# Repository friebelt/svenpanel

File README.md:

# svenpanel
Hardware Version of the Shrine (originally made by  cubuss)<br>
https://theshrine.pw/<br>
https://svenpanel.de/<br>
https://github.com/kidzki/theshrine_v3<br>

Pictures and documentation will follow (hopefully)

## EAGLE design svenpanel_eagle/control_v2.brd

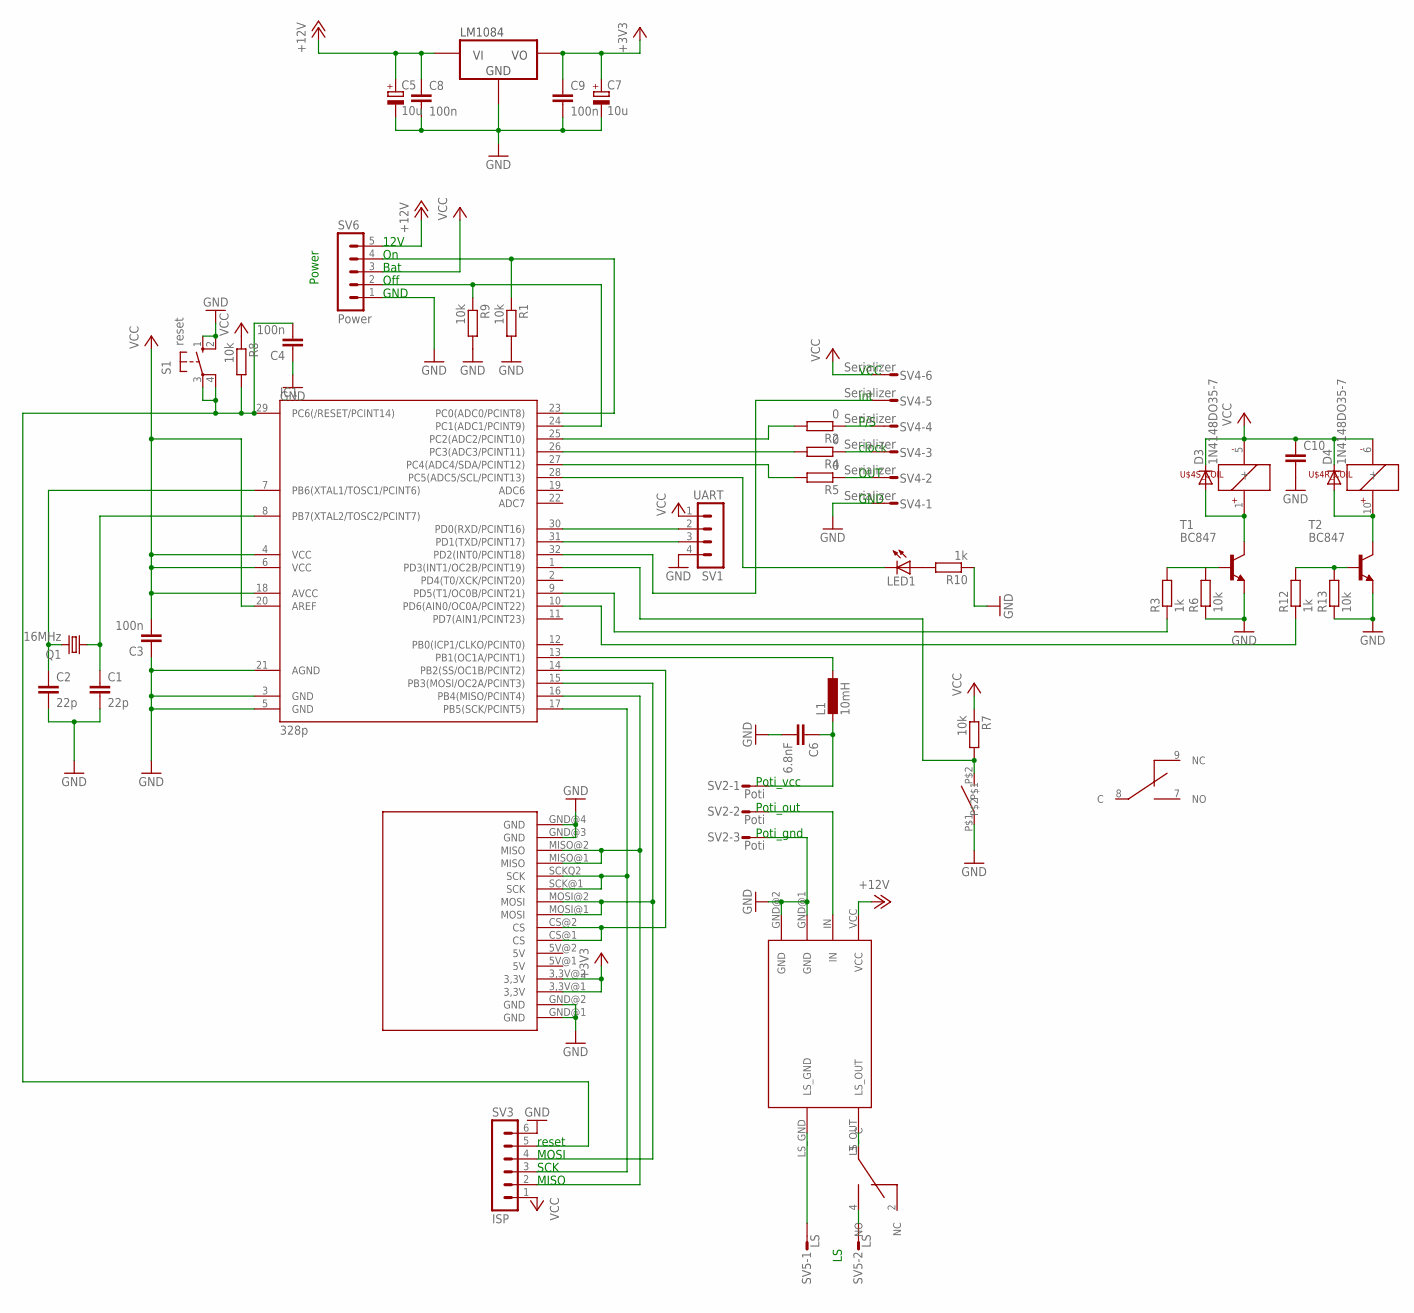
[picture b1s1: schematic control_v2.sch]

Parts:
C1, C2: 22p; C1206
C3, C4, C8, C9: 100n; C1206
C5, C7: 10u; E2,5-7
C6: 6.8nF; C050-024X044
C10: C-EUC1206; C1206
D3, D4: 1N4148DO35-7; DO35-7
IC1: 328p; TQFP32-08
L1: 10mH; 0207/5V
LED1: LEDCHIPLED_1206; CHIPLED_1206
Q1: 16MHz; HC49UP
R1, R6, R7, R8, R9, R13: 10k; M1206
R2, R4, R5: 0; M1206
R3, R10, R12: 1k; M1206
S1: reset; B3F-10XX
SV1: UART; MA04-1
SV2: Poti; S03P
SV3: ISP; MA06-1
SV4: Serializer; S06P
SV5: LS; S02P
SV6: Power; MA05-1
T1, T2: BC847; SOT23-BEC
U$1: TILT
U$2: AMP
U$3: SD_CARD_HOLDER
U$4: EB2-4.5TNU; 10PIN_SMD_RELAY
U$5: LD1117; TO220V

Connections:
+3V3: C7.+, C9.1, U$3.3,3V@1 (3,3V), U$3.3,3V@2 (3,3V), U$5.2 (VO)
+12V: C5.+, C8.1, SV6.5, U$2.VCC, U$5.3 (VI)
GND: C1.2, C2.2, C3.1, C4.1, C5.-, C6.2, C7.-, C8.2, C9.2, C10.2, IC1.3 (GND), IC1.5 (GND), IC1.21 (AGND), R1.2, R6.1, R9.2, R10.1, R13.1, S1.1 (S), S1.2 (S1), SV1.4, SV2.3, SV3.6, SV4.1, SV6.1, T1.E, T2.E, U$1.P$1, U$2.GND@1 (GND), U$2.GND@2 (GND), U$3.GND@1 (GND), U$3.GND@2 (GND), U$3.GND@3 (GND), U$3.GND@4 (GND), U$5.1 (GND)
unnamed: U$2.LS_OUT, U$4.3 (C)
unnamed: IC1.30 (PD0(RXD/PCINT16)), SV1.2
unnamed: IC1.31 (PD1(TXD/PCINT17)), SV1.3
unnamed: C2.1, IC1.7 (PB6(XTAL1/TOSC1/PCINT6)), Q1.2
unnamed: C1.1, IC1.8 (PB7(XTAL2/TOSC2/PCINT7)), Q1.1
unnamed: IC1.14 (PB2(SS/OC1B/PCINT2)), U$3.CS@1 (CS), U$3.CS@2 (CS)
unnamed: IC1.15 (PB3(MOSI/OC2A/PCINT3)), SV3.4, U$3.MOSI@1 (MOSI), U$3.MOSI@2 (MOSI)
unnamed: IC1.16 (PB4(MISO/PCINT4)), SV3.2, U$3.MISO@1 (MISO), U$3.MISO@2 (MISO)
unnamed: IC1.17 (PB5(SCK/PCINT5)), SV3.3, U$3.SCK@1 (SCK), U$3.SCKQ2 (SCK)
unnamed: SV5.2, U$4.4 (NO)
unnamed: IC1.13 (PB1(OC1A/PCINT1)), L1.1
unnamed: C6.1, L1.2, SV2.1
unnamed: SV5.1, U$2.LS_GND
unnamed: SV2.2, U$2.IN
unnamed: IC1.23 (PC0(ADC0/PCINT8)), R1.1, SV6.4
unnamed: R5.1, SV4.2
unnamed: R4.1, SV4.3
unnamed: R2.1, SV4.4
unnamed: IC1.32 (PD2(INT0/PCINT18)), SV4.5
unnamed: IC1.25 (PC2(ADC2/PCINT10)), R2.2
unnamed: IC1.26 (PC3(ADC3/PCINT11)), R4.2
unnamed: IC1.24 (PC1(ADC1/PCINT9)), R9.1, SV6.2
unnamed: D3.A, T1.C, U$4.1 (+)
unnamed: IC1.27 (PC4(ADC4/SDA/PCINT12)), R5.2
unnamed: IC1.1 (PD3(INT1/OC2B/PCINT19)), R7.2, U$1.P$2
unnamed: LED1.A, R10.2
unnamed: R12.2, R13.2, T2.B
unnamed: IC1.28 (PC5(ADC5/SCL/PCINT13)), LED1.C
unnamed: IC1.10 (PD6(AIN0/OC0A/PCINT22)), R12.1
unnamed: C4.2, IC1.29 (PC6(/RESET/PCINT14)), R8.2, S1.3, S1.4 (P1), SV3.5
unnamed: IC1.9 (PD5(T1/OC0B/PCINT21)), R3.1
unnamed: D4.A, T2.C, U$4.10 (+)
unnamed: R3.2, R6.2, T1.B
VCC: C3.2, C10.1, D3.C, D4.C, IC1.4 (VCC), IC1.6 (VCC), IC1.18 (AVCC), IC1.20 (AREF), R7.1, R8.1, SV1.1, SV3.1, SV4.6, SV6.3, U$4.5 (-), U$4.6 (-)

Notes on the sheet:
Poti_vcc
Poti_out
Poti_gnd
12V
Off
GND
Bat
OUT
clock
P/S
int
VCC
Power
reset
MOSI
SCK
MISO

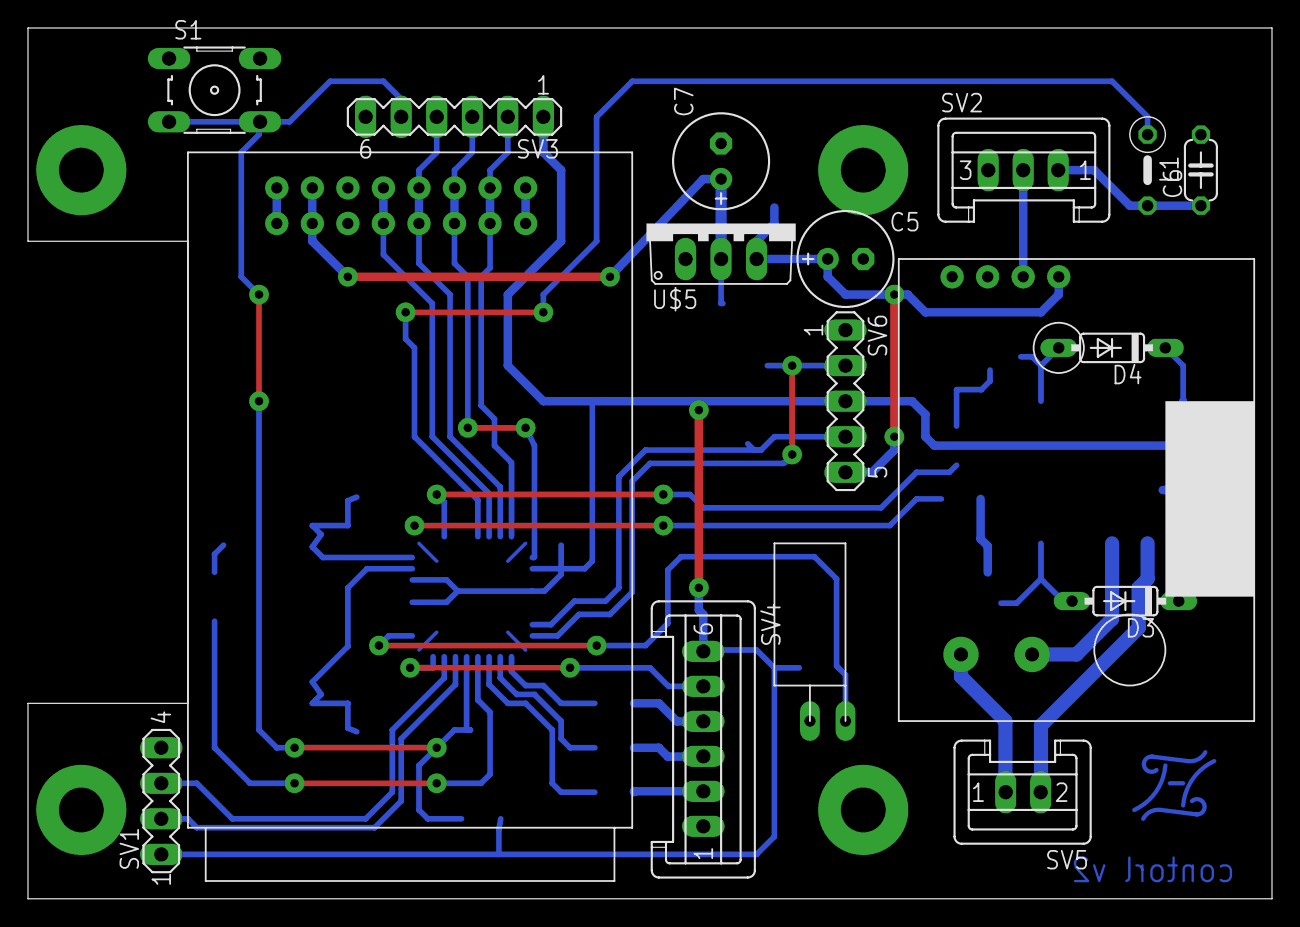
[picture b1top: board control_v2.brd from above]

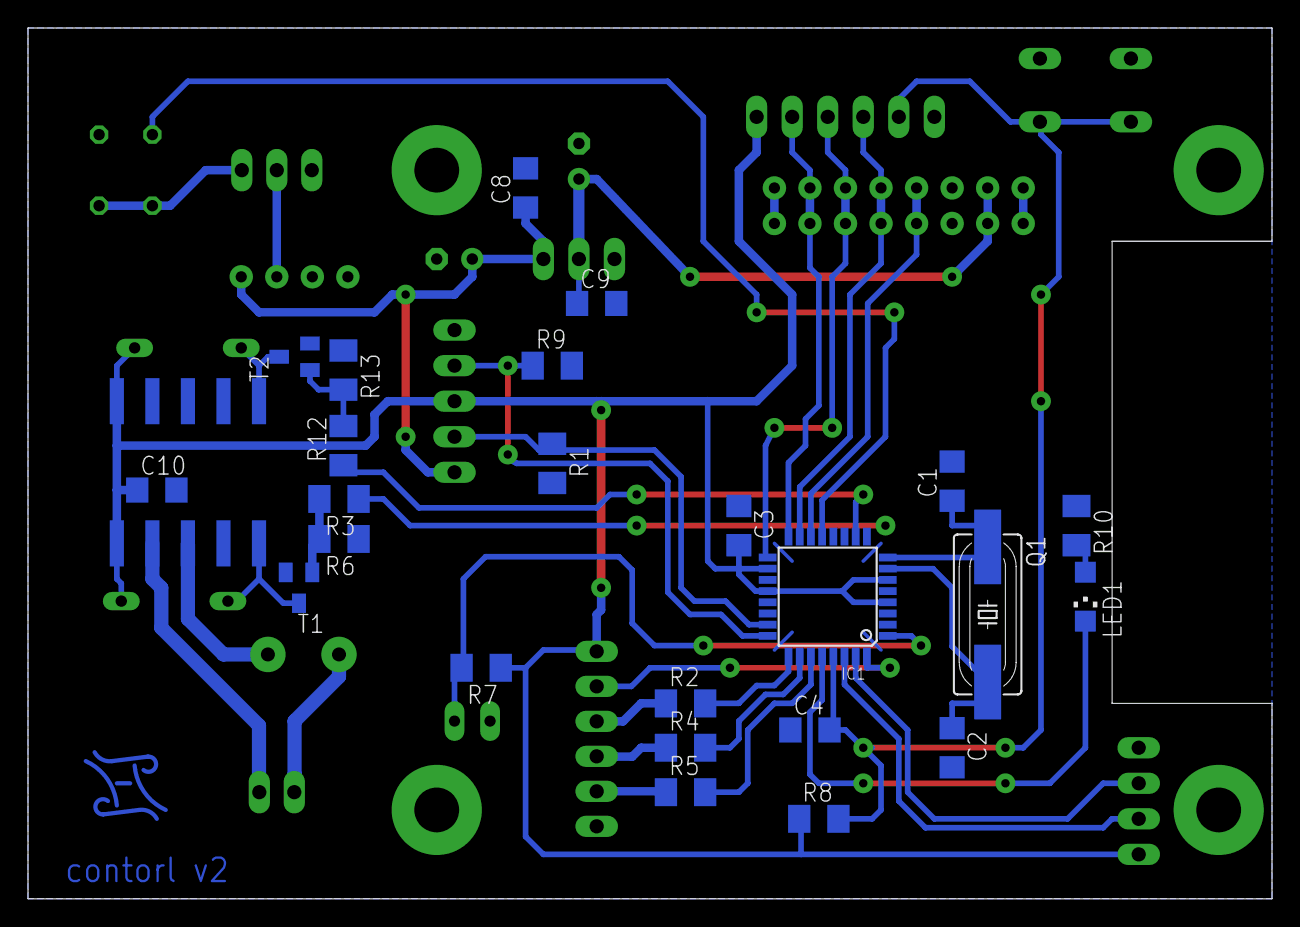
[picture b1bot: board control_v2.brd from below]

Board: 2 copper layers, 88.9 x 62.2 mm, 42 parts (25 on the bottom side), 37 nets.

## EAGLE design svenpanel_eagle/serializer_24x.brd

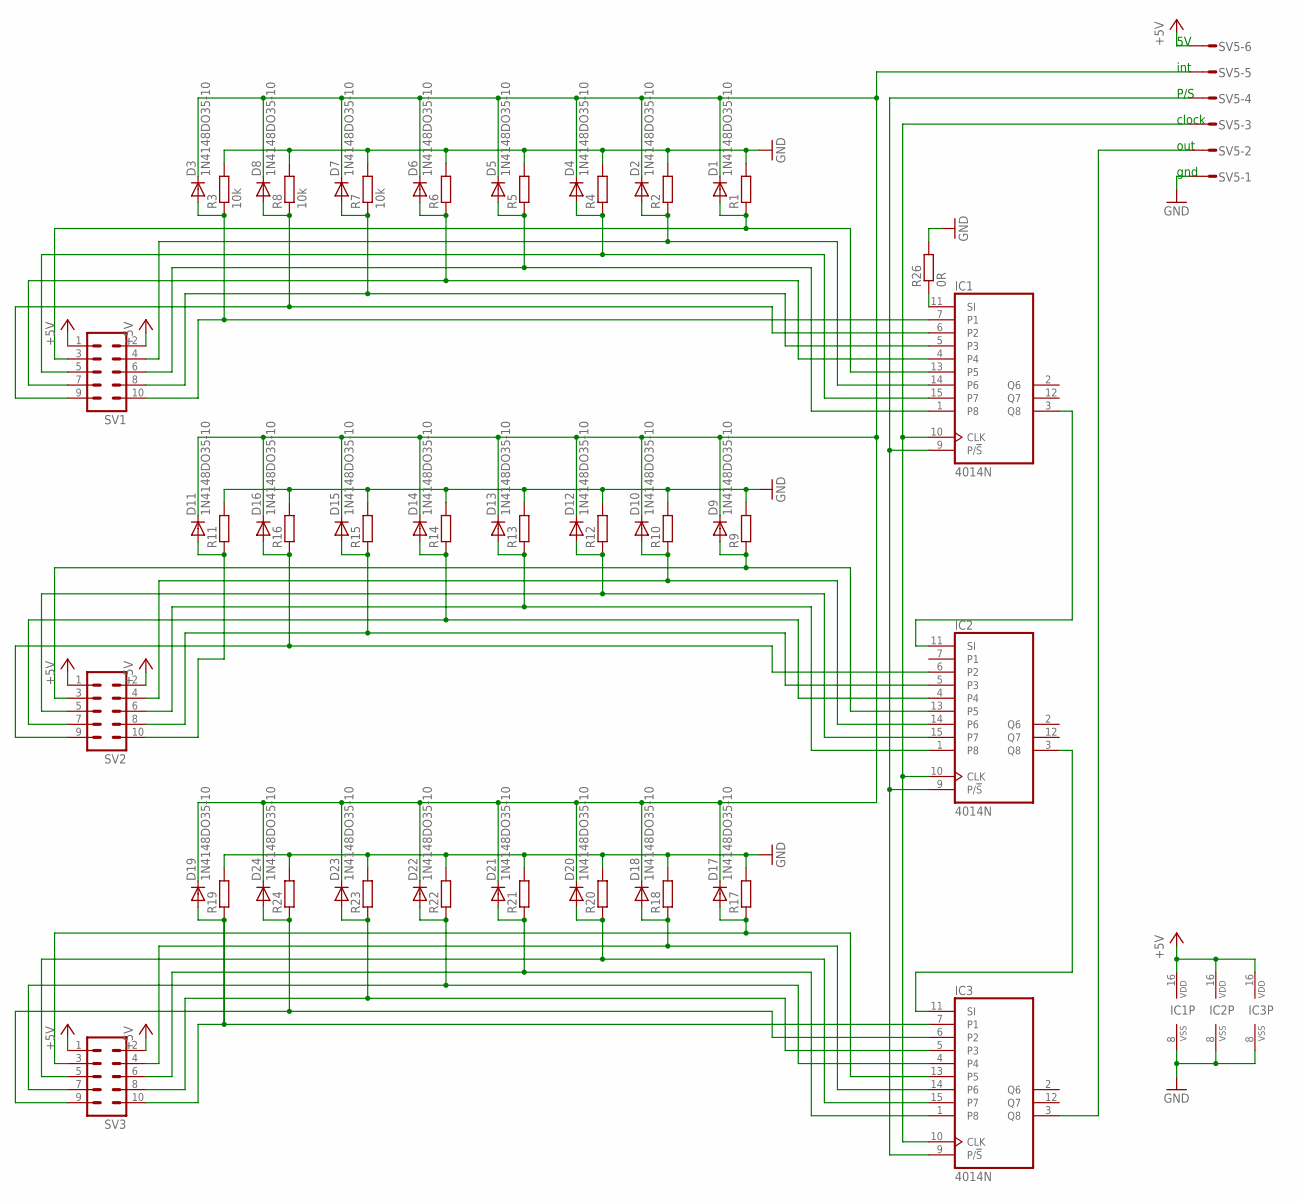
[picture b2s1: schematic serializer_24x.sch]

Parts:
D1, D2, D3, D4, D5, D6, D7, D8, D9, D10, D11, D12, D13, D14, D15, D16, D17, D18, D19, D20, D21, D22, D23, D24: 1N4148DO35-10; DO35-10
IC1, IC2, IC3: 4014N; DIL16
R1, R2, R4, R5, R6, R9, R10, R11, R12, R13, R14, R15, R16, R17, R18, R19, R20, R21, R22, R23, R24: R-EU_M1206; M1206
R3, R7, R8: 10k; M1206
R26: 0R; M1206
SV1, SV2, SV3: ML10
SV5: S06P

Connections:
+5V: IC1.16 (VDD), IC2.16 (VDD), IC3.16 (VDD), SV1.1, SV1.2, SV2.1, SV2.2, SV3.1, SV3.2, SV5.6
GND: IC1.8 (VSS), IC2.8 (VSS), IC3.8 (VSS), R1.2, R2.2, R3.2, R4.2, R5.2, R6.2, R7.2, R8.2, R9.2, R10.2, R11.2, R12.2, R13.2, R14.2, R15.2, R16.2, R17.2, R18.2, R19.2, R20.2, R21.2, R22.2, R23.2, R24.2, R26.2, SV5.1
unnamed: D1.A, IC1.13 (P5), R1.1, SV1.3
unnamed: D2.A, IC1.14 (P6), R2.1, SV1.4
unnamed: D9.A, IC2.13 (P5), R9.1, SV2.3
unnamed: D10.A, IC2.14 (P6), R10.1, SV2.4
unnamed: D12.A, IC2.15 (P7), R12.1, SV2.5
unnamed: D13.A, IC2.1 (P8), R13.1, SV2.6
unnamed: D14.A, IC2.4, R14.1, SV2.7
unnamed: D15.A, IC2.5 (P3), R15.1, SV2.8
unnamed: D16.A, IC2.6 (P2), R16.1, SV2.9
unnamed: IC2.3 (Q8), IC3.11 (SI)
unnamed: IC1.10 (CLK), IC2.10 (CLK), IC3.10 (CLK), SV5.3
unnamed: D17.A, IC3.13 (P5), R17.1, SV3.3
unnamed: D18.A, IC3.14 (P6), R18.1, SV3.4
unnamed: D1.C, D2.C, D3.C, D4.C, D5.C, D6.C, D7.C, D8.C, D9.C, D10.C, D11.C, D12.C, D13.C, D14.C, D15.C, D16.C, D17.C, D18.C, D19.C, D20.C, D21.C, D22.C, D23.C, D24.C, SV5.5
unnamed: D19.A, IC3.7 (P1), R19.1, SV3.10
unnamed: D20.A, IC3.15 (P7), R20.1, SV3.5
unnamed: D21.A, IC3.1 (P8), R21.1, SV3.6
unnamed: D22.A, IC3.4, R22.1, SV3.7
unnamed: D23.A, IC3.5 (P3), R23.1, SV3.8
unnamed: D24.A, IC3.6 (P2), R24.1, SV3.9
unnamed: IC1.11 (SI), R26.1
unnamed: D11.A, R11.1, SV2.10
unnamed: IC3.3 (Q8), SV5.2
unnamed: D3.A, IC1.7 (P1), R3.1, SV1.10
unnamed: IC1.9 (P/!S), IC2.9 (P/!S), IC3.9 (P/!S), SV5.4
unnamed: D4.A, IC1.15 (P7), R4.1, SV1.5
unnamed: D5.A, IC1.1 (P8), R5.1, SV1.6
unnamed: D6.A, IC1.4, R6.1, SV1.7
unnamed: D7.A, IC1.5 (P3), R7.1, SV1.8
unnamed: D8.A, IC1.6 (P2), R8.1, SV1.9
unnamed: IC1.3 (Q8), IC2.11 (SI)

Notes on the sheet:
out
clock
gnd
P/S
int

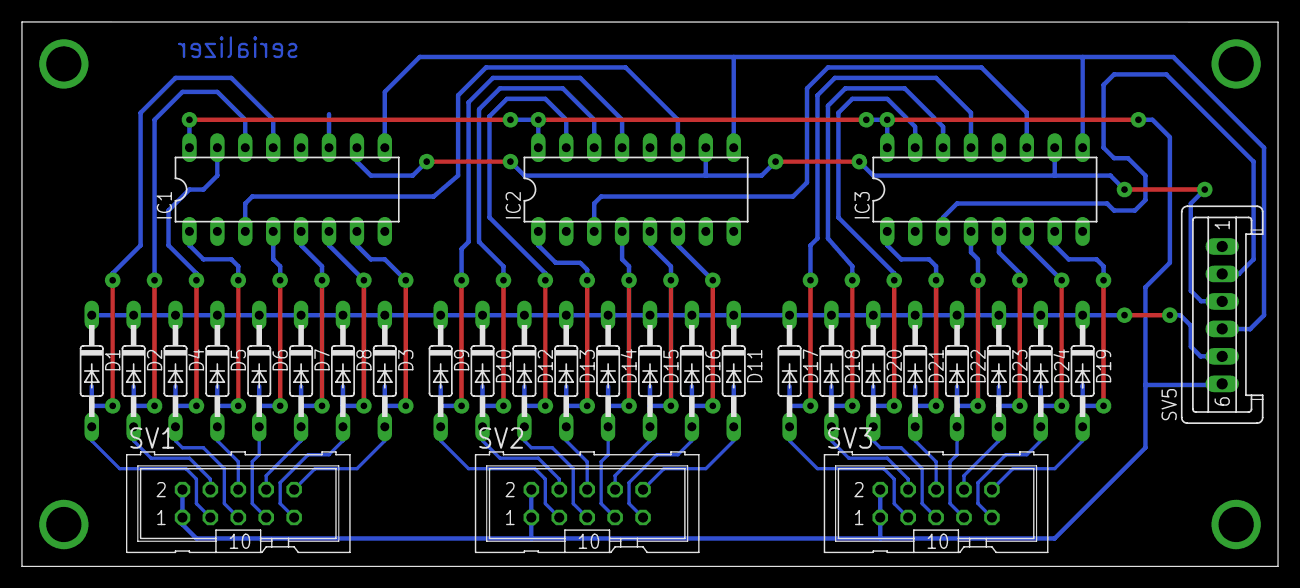
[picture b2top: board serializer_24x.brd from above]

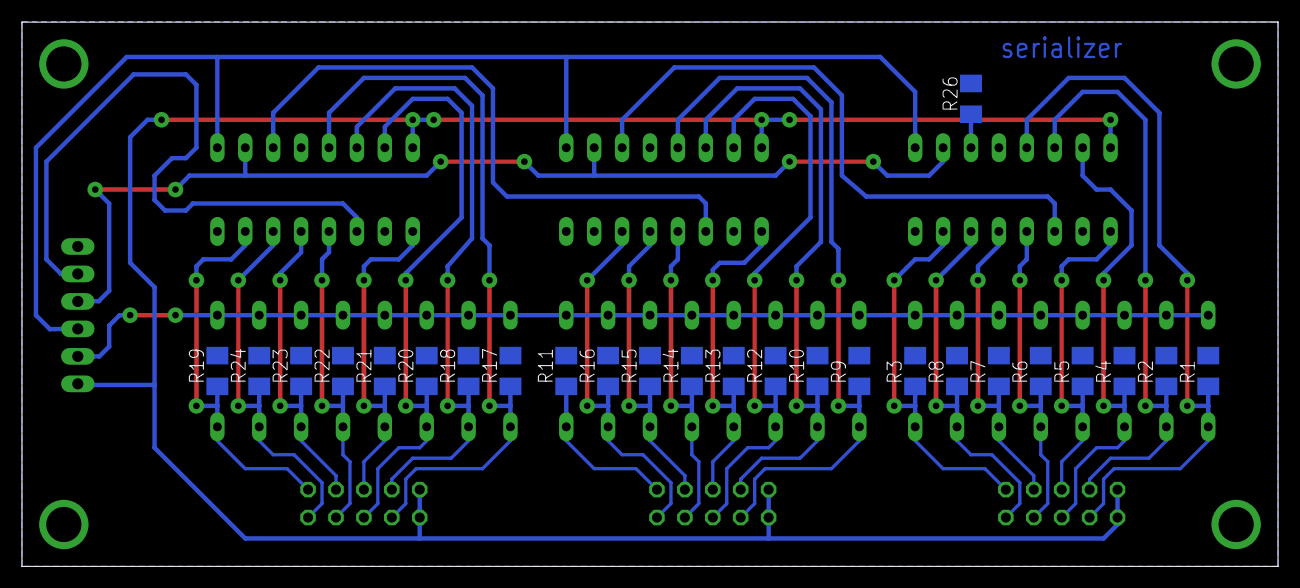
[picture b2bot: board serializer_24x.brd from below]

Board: 2 copper layers, 114.3 x 49.5 mm, 56 parts (25 on the bottom side), 33 nets.

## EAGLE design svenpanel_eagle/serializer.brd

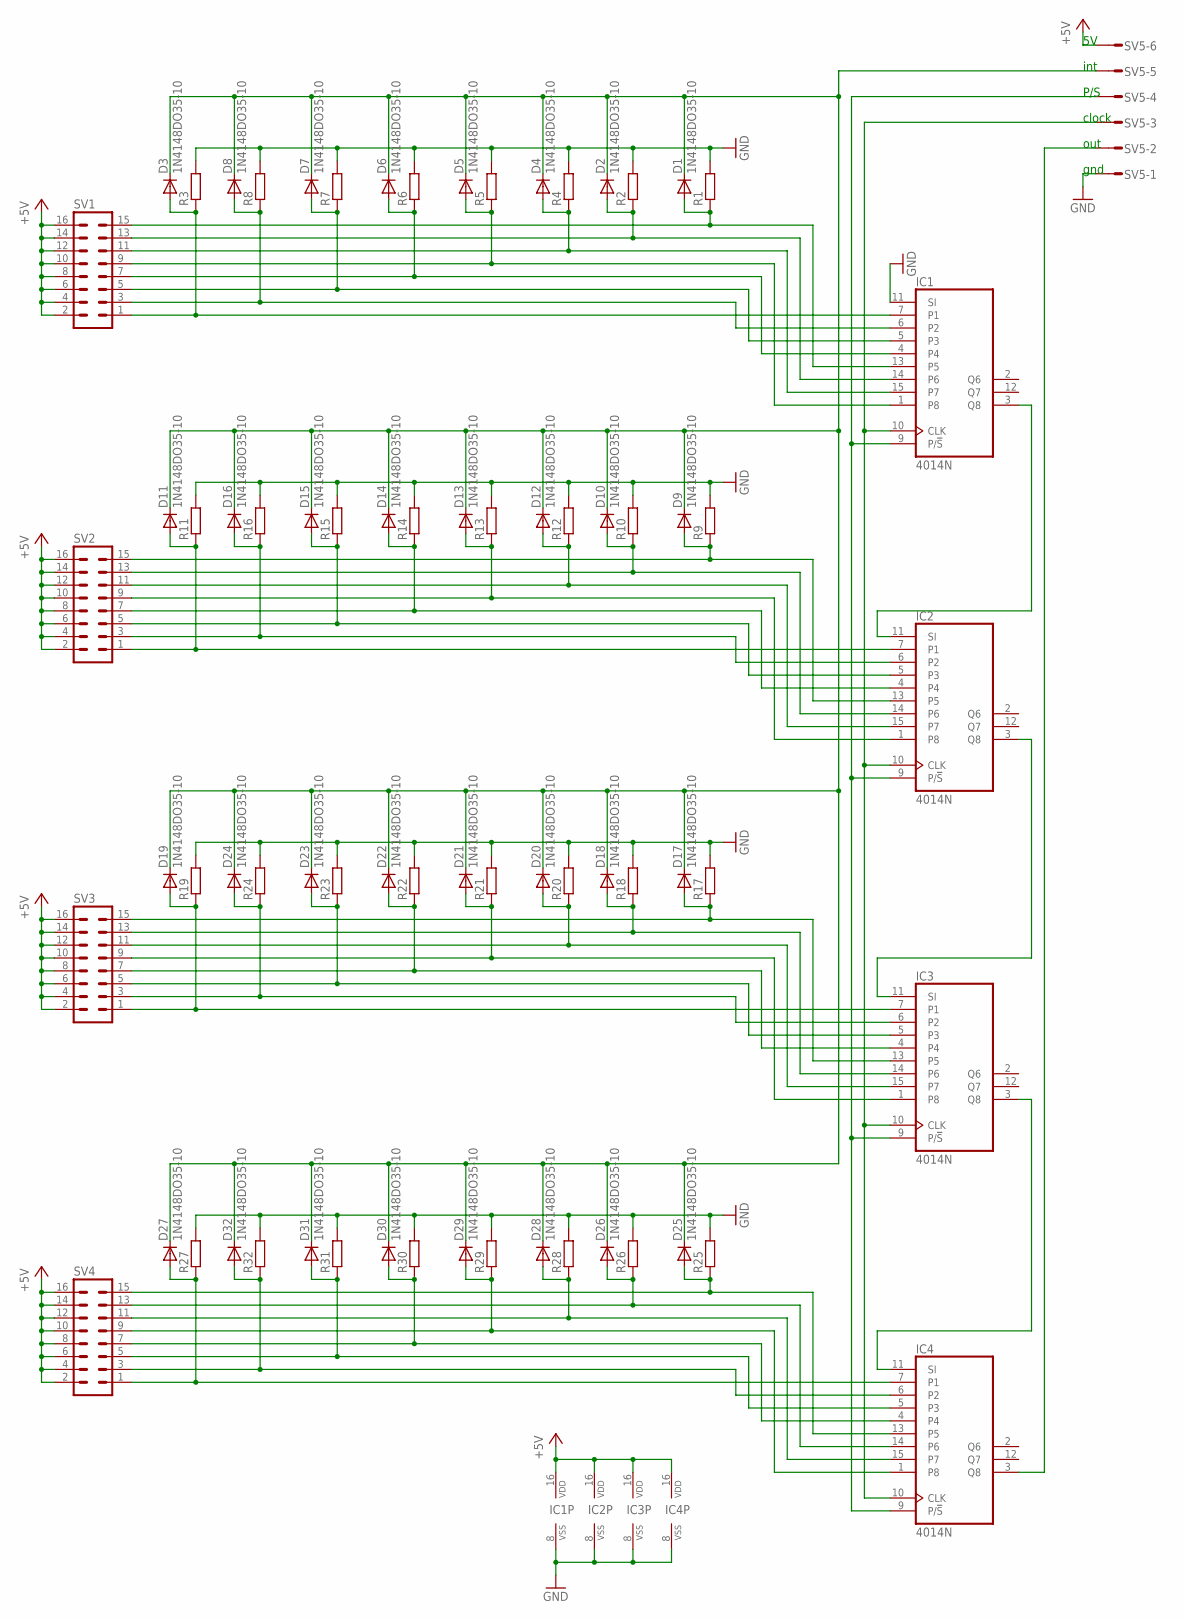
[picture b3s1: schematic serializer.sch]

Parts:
D1, D2, D3, D4, D5, D6, D7, D8, D9, D10, D11, D12, D13, D14, D15, D16, D17, D18, D19, D20, D21, D22, D23, D24, D25, D26, D27, D28, D29, D30, D31, D32: 1N4148DO35-10; DO35-10
IC1, IC2, IC3, IC4: 4014N; DIL16
R1, R2, R3, R4, R5, R6, R7, R8, R9, R10, R11, R12, R13, R14, R15, R16, R17, R18, R19, R20, R21, R22, R23, R24, R25, R26, R27, R28, R29, R30, R31, R32: R-EU_M1206; M1206
SV1, SV2, SV3, SV4: MA08-2
SV5: S06P

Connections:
+5V: IC1.16 (VDD), IC2.16 (VDD), IC3.16 (VDD), IC4.16 (VDD), SV1.2, SV1.4, SV1.6, SV1.8, SV1.10, SV1.12, SV1.14, SV1.16, SV2.2, SV2.4, SV2.6, SV2.8, SV2.10, SV2.12, SV2.14, SV2.16, SV3.2, SV3.4, SV3.6, SV3.8, SV3.10, SV3.12, SV3.14, SV3.16, SV4.2, SV4.4, SV4.6, SV4.8, SV4.10, SV4.12, SV4.14, SV4.16, SV5.6
GND: IC1.8 (VSS), IC1.11 (SI), IC2.8 (VSS), IC3.8 (VSS), IC4.8 (VSS), R1.2, R2.2, R3.2, R4.2, R5.2, R6.2, R7.2, R8.2, R9.2, R10.2, R11.2, R12.2, R13.2, R14.2, R15.2, R16.2, R17.2, R18.2, R19.2, R20.2, R21.2, R22.2, R23.2, R24.2, R25.2, R26.2, R27.2, R28.2, R29.2, R30.2, R31.2, R32.2, SV5.1
unnamed: D1.A, IC1.13 (P5), R1.1, SV1.15
unnamed: D2.A, IC1.14 (P6), R2.1, SV1.13
unnamed: D9.A, IC2.13 (P5), R9.1, SV2.15
unnamed: D10.A, IC2.14 (P6), R10.1, SV2.13
unnamed: D11.A, IC2.7 (P1), R11.1, SV2.1
unnamed: D12.A, IC2.15 (P7), R12.1, SV2.11
unnamed: D13.A, IC2.1 (P8), R13.1, SV2.9
unnamed: D14.A, IC2.4, R14.1, SV2.7
unnamed: D15.A, IC2.5 (P3), R15.1, SV2.5
unnamed: D16.A, IC2.6 (P2), R16.1, SV2.3
unnamed: IC2.3 (Q8), IC3.11 (SI)
unnamed: IC1.10 (CLK), IC2.10 (CLK), IC3.10 (CLK), IC4.10 (CLK), SV5.3
unnamed: D17.A, IC3.13 (P5), R17.1, SV3.15
unnamed: D18.A, IC3.14 (P6), R18.1, SV3.13
unnamed: D1.C, D2.C, D3.C, D4.C, D5.C, D6.C, D7.C, D8.C, D9.C, D10.C, D11.C, D12.C, D13.C, D14.C, D15.C, D16.C, D17.C, D18.C, D19.C, D20.C, D21.C, D22.C, D23.C, D24.C, D25.C, D26.C, D27.C, D28.C, D29.C, D30.C, D31.C, D32.C, SV5.5
unnamed: D19.A, IC3.7 (P1), R19.1, SV3.1
unnamed: D20.A, IC3.15 (P7), R20.1, SV3.11
unnamed: D21.A, IC3.1 (P8), R21.1, SV3.9
unnamed: D22.A, IC3.4, R22.1, SV3.7
unnamed: D23.A, IC3.5 (P3), R23.1, SV3.5
unnamed: D24.A, IC3.6 (P2), R24.1, SV3.3
unnamed: IC3.3 (Q8), IC4.11 (SI)
unnamed: D25.A, IC4.13 (P5), R25.1, SV4.15
unnamed: D26.A, IC4.14 (P6), R26.1, SV4.13
unnamed: D27.A, IC4.7 (P1), R27.1, SV4.1
unnamed: D28.A, IC4.15 (P7), R28.1, SV4.11
unnamed: D29.A, IC4.1 (P8), R29.1, SV4.9
unnamed: D30.A, IC4.4, R30.1, SV4.7
unnamed: D31.A, IC4.5 (P3), R31.1, SV4.5
unnamed: D32.A, IC4.6 (P2), R32.1, SV4.3
unnamed: IC4.3 (Q8), SV5.2
unnamed: D3.A, IC1.7 (P1), R3.1, SV1.1
unnamed: IC1.9 (P/!S), IC2.9 (P/!S), IC3.9 (P/!S), IC4.9 (P/!S), SV5.4
unnamed: D4.A, IC1.15 (P7), R4.1, SV1.11
unnamed: D5.A, IC1.1 (P8), R5.1, SV1.9
unnamed: D6.A, IC1.4, R6.1, SV1.7
unnamed: D7.A, IC1.5 (P3), R7.1, SV1.5
unnamed: D8.A, IC1.6 (P2), R8.1, SV1.3
unnamed: IC1.3 (Q8), IC2.11 (SI)

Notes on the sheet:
out
clock
gnd
P/S
int

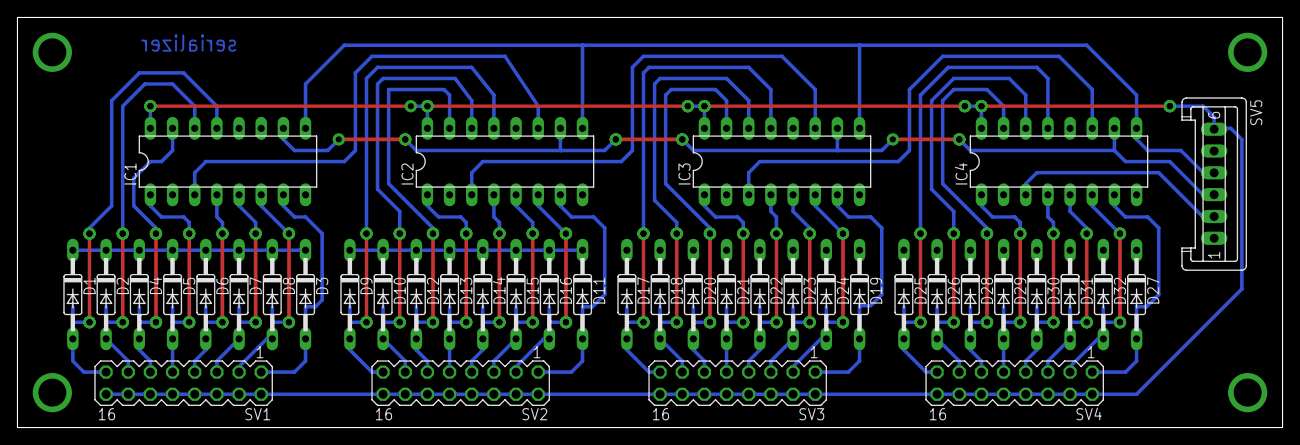
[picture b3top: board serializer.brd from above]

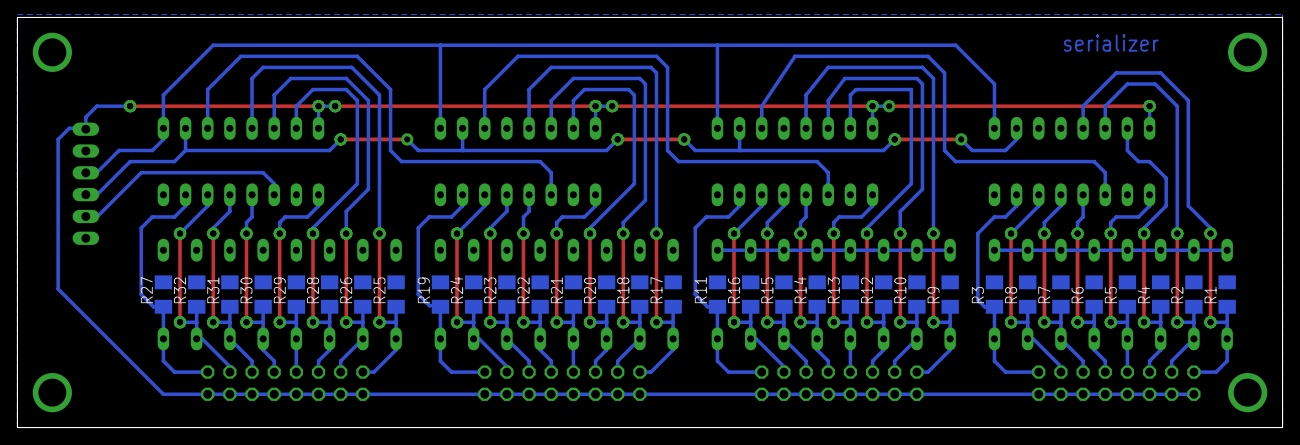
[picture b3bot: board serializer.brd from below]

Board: 2 copper layers, 145.0 x 47.0 mm, 73 parts (32 on the bottom side), 41 nets.

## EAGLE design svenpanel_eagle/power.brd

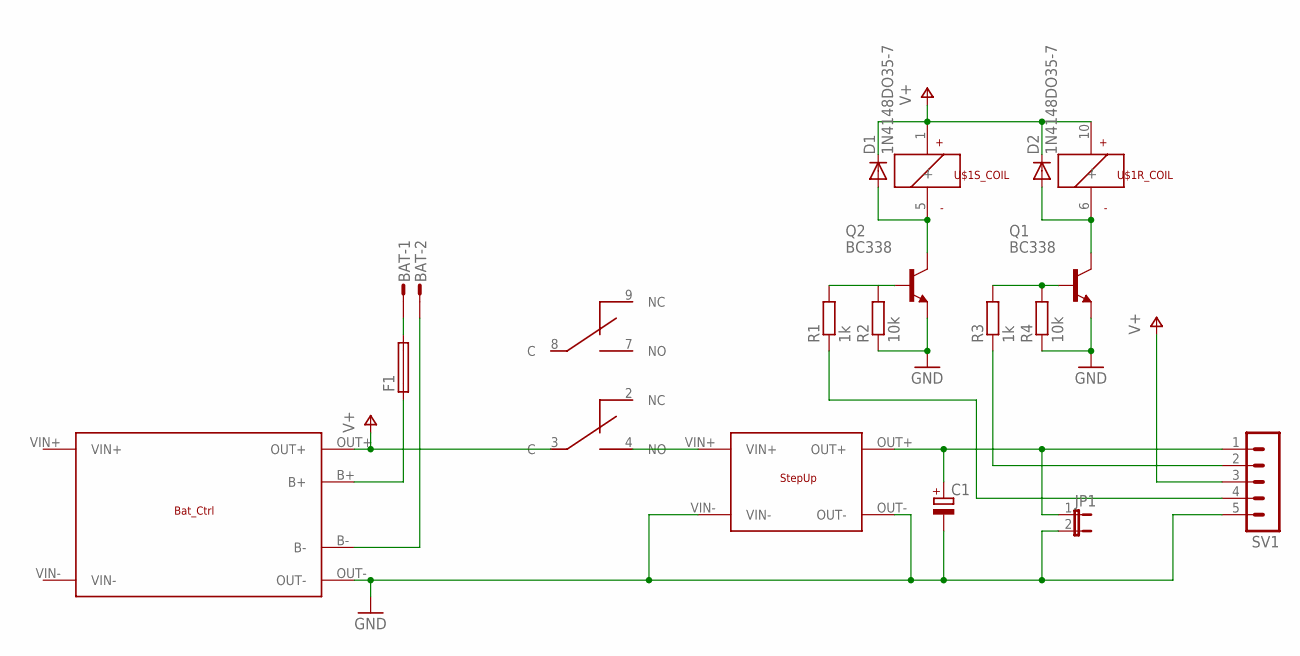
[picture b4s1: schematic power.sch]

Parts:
BAT: S02P
C1: CPOL-EUE3.5-8; E3,5-8
D1, D2: 1N4148DO35-7; DO35-7
F1: SH22,5
JP1: JP1E; JP1
Q1, Q2: BC338; TO92-EBC
R1, R3: 1k; 0204/7
R2, R4: 10k; M1206
SV1: MA05-1
U$1: EB2-4.5TNU; 10PIN_SMD_RELAY
U$2: STEP_UP
U$3: BAT_CTRL; BAT_CONTR

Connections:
GND: C1.-, JP1.2, Q1.E, Q2.E, R2.1, R4.1, SV1.5, U$2.OUT-, U$2.VIN-, U$3.OUT-
unnamed: D2.A, Q1.C, U$1.6 (-)
unnamed: D1.A, Q2.C, U$1.5 (-)
unnamed: Q2.B, R1.2, R2.2
unnamed: Q1.B, R3.2, R4.2
unnamed: BAT.1, F1.2
unnamed: F1.1, U$3.B+
unnamed: BAT.2, U$3.B-
unnamed: U$1.4 (NO), U$2.VIN+
unnamed: C1.+, JP1.1, SV1.1, U$2.OUT+
unnamed: R3.1, SV1.2
unnamed: R1.1, SV1.4
V+: D1.C, D2.C, SV1.3, U$1.1 (+), U$1.3 (C), U$1.10 (+), U$3.OUT+

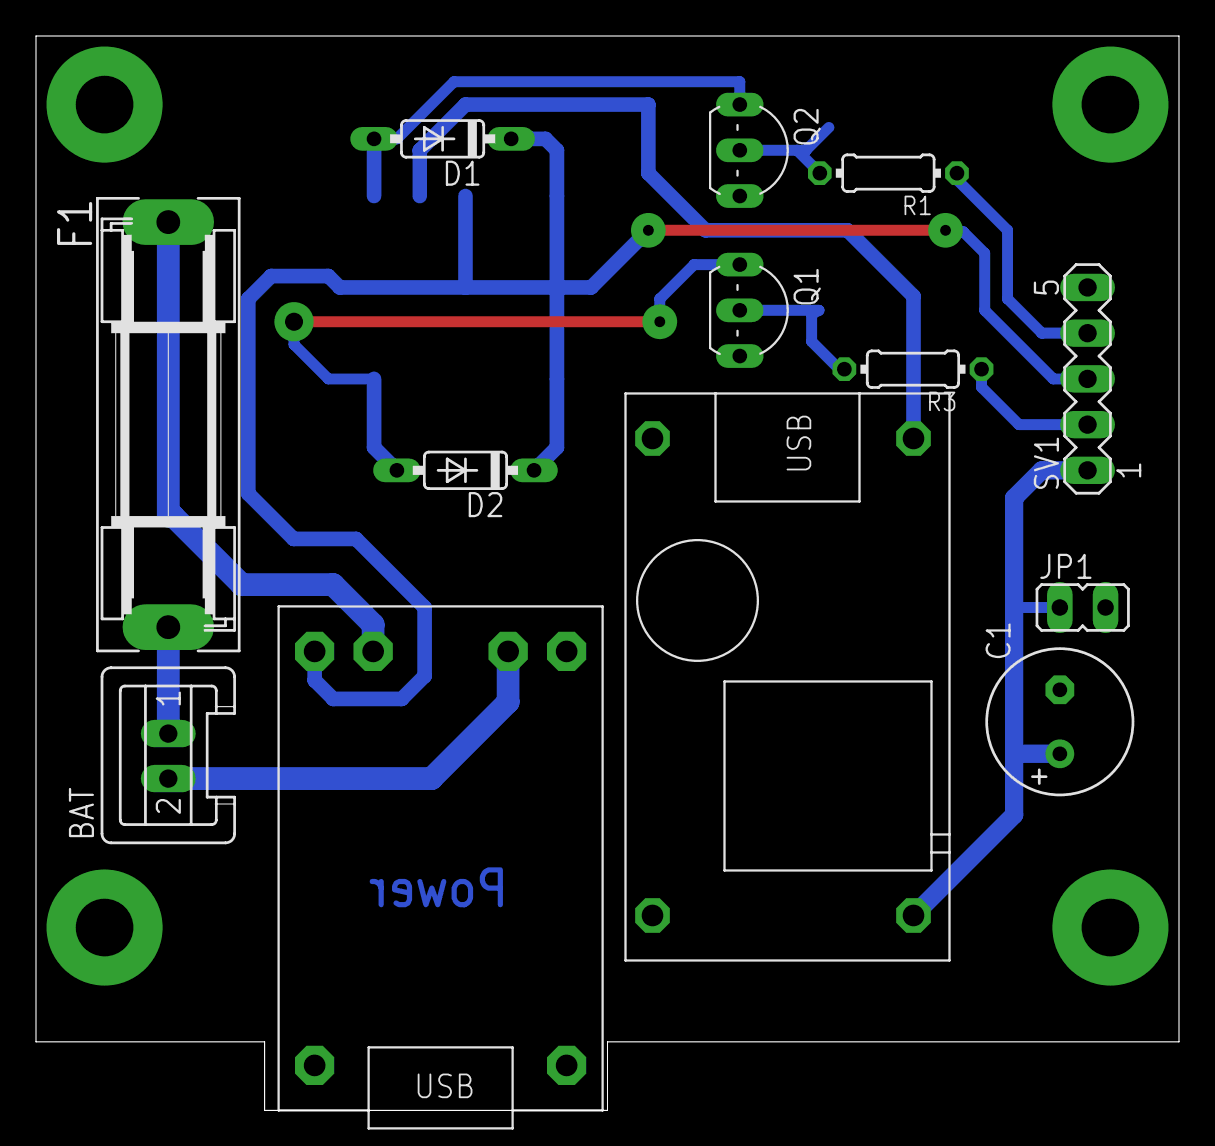
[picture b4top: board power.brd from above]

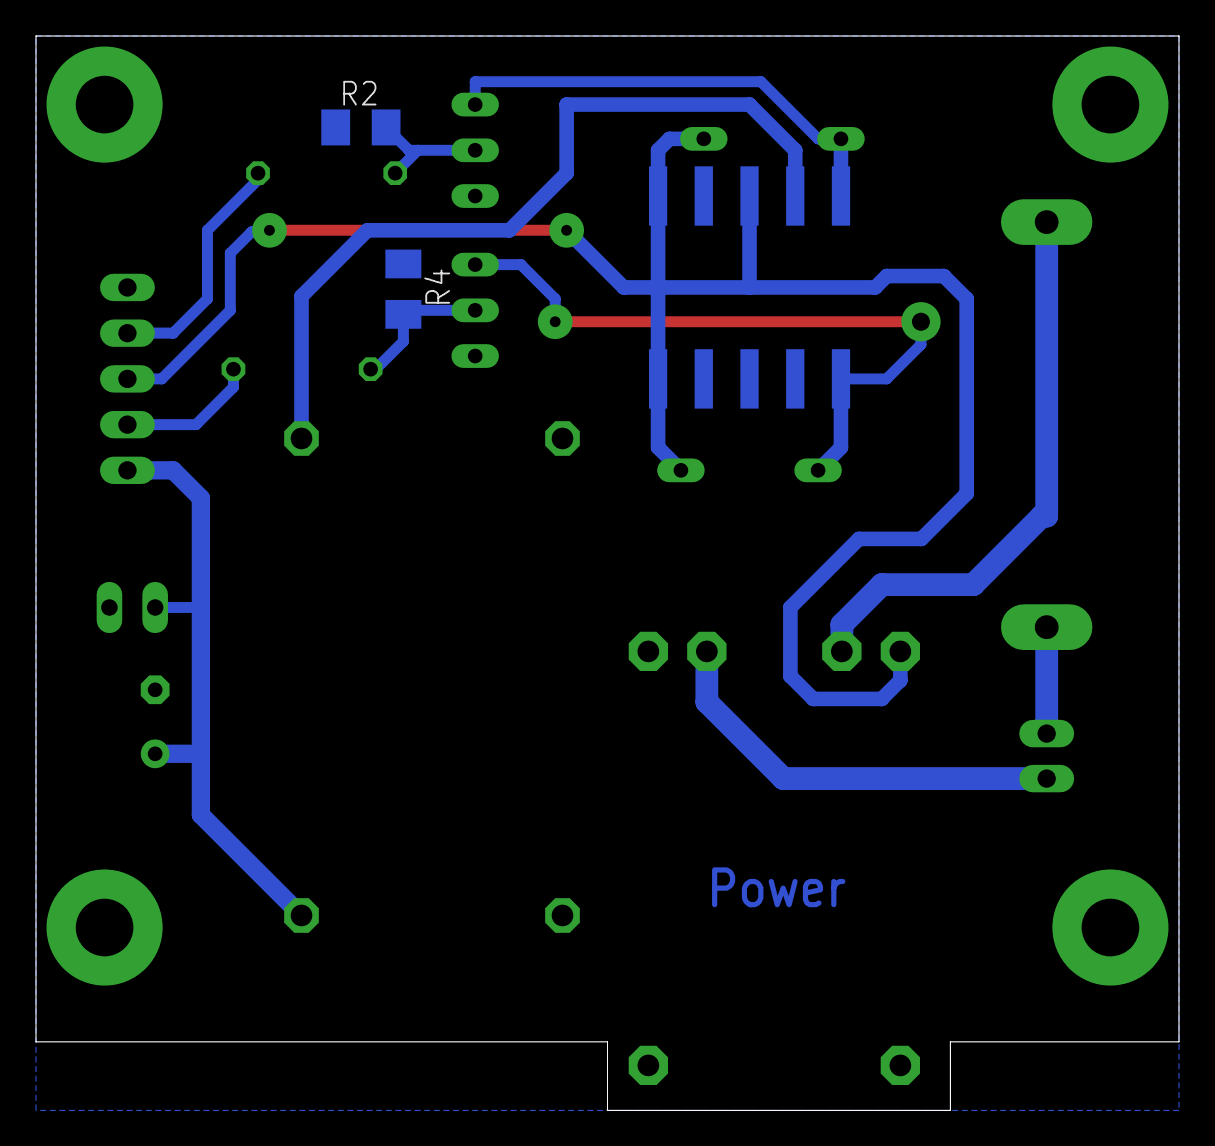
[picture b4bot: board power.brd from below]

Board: 2 copper layers, 63.5 x 59.7 mm, 16 parts (3 on the bottom side), 13 nets.

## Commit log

2020-03-20 Tests with nano look very promising, low power and SD Card working
2020-03-20 now plays audio, current went up to 770uA, investigating...
2020-03-20 found it! (disable audio output after Playback). Back to 43uA
2020-03-20 using sdfat lib, audio playing nicely, standby current still low
2020-04-02 forgot to commit, dont know what I have done
